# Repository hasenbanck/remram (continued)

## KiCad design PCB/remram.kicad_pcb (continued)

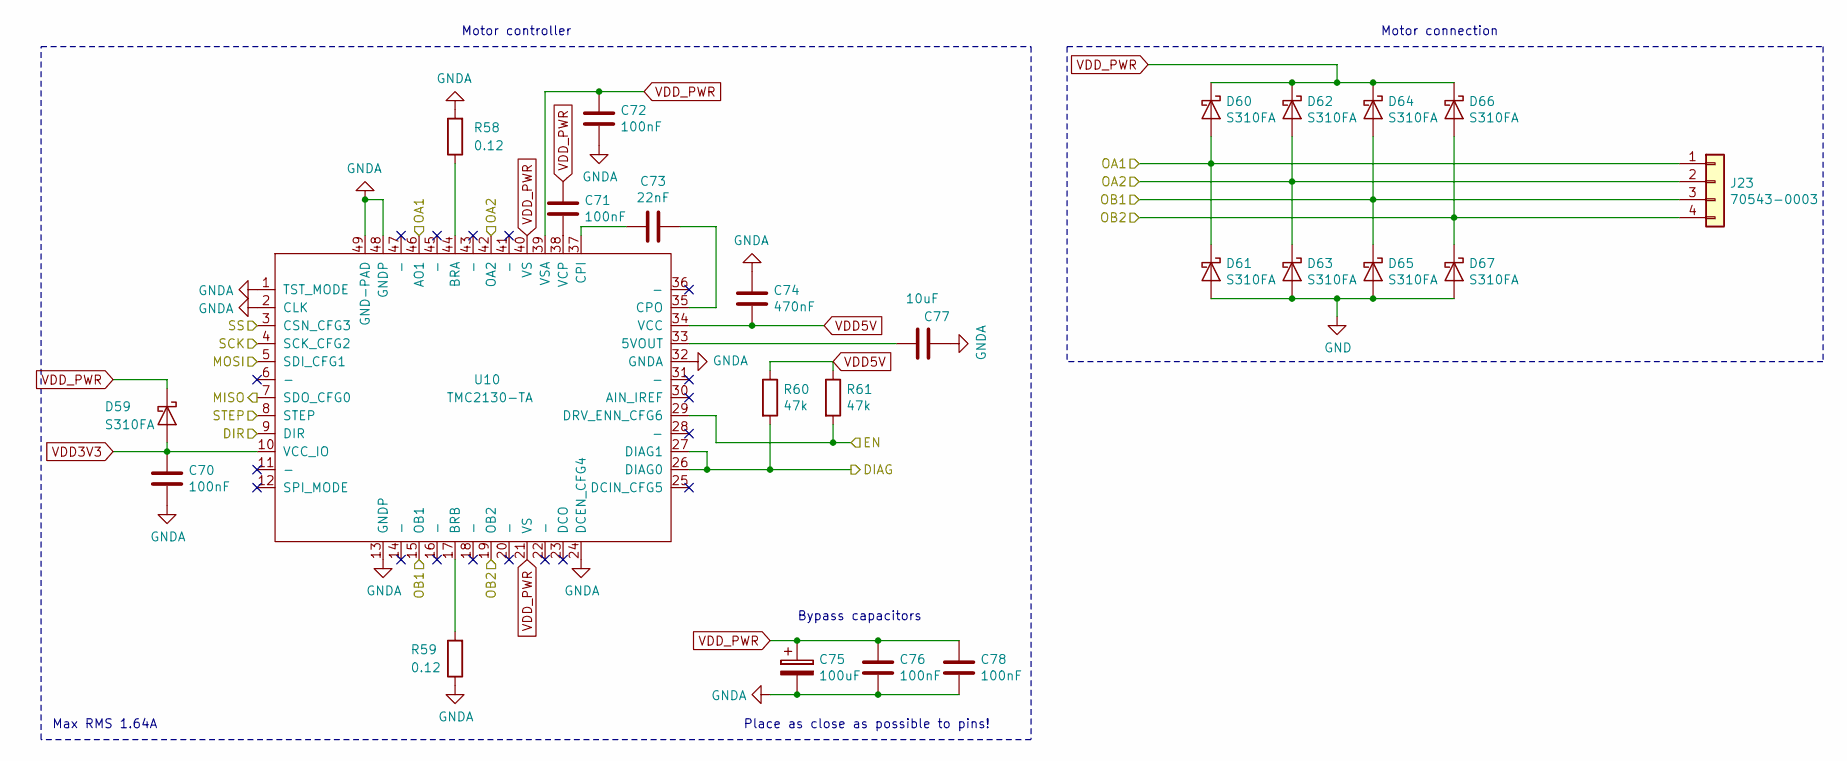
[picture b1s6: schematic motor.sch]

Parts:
C43, C44, C45, C49, C51: 100nF; C_0603_1608Metric
C46: 22nF; C_0603_1608Metric
C47: 470nF; C_0603_1608Metric
C48: 100uF; CP_Radial_D6.3mm_P2.50mm
C50: 10uF; C_0603_1608Metric
D32, D33, D34, D35, D36, D37, D38, D39, D40: S310FA; D_SOD-123
J20: 70543-0003
R46, R47: 0.12; R_1206_3216Metric
R48, R49: 47k; R_0603_1608Metric
U7: TMC2130-TA; TQFP-48-1EP_7x7mm_P0.5mm_EP4.8x4.8mm-Heatsink

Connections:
/MCU/MISO: U7.7 (SDO_CFG0); also elsewhere on the board
/MCU/MOSI: U7.5 (SDI_CFG1); also elsewhere on the board
/MCU/SCK: U7.4 (SCK_CFG2); also elsewhere on the board
/Motor X/DIAG: R48.2, U7.26 (DIAG0), U7.27 (DIAG1); also elsewhere on the board
/Motor X/DIR: U7.9 (DIR); also elsewhere on the board
/Motor X/EN: R49.2, U7.29 (DRV_ENN_CFG6); also elsewhere on the board
/Motor X/OA1: D33.2 (A), D34.1 (K), J20.1, U7.46 (AO1)
/Motor X/OA2: D35.2 (A), D36.1 (K), J20.2, U7.42 (OA2)
/Motor X/OB1: D37.2 (A), D38.1 (K), J20.3, U7.15 (OB1)
/Motor X/OB2: D39.2 (A), D40.1 (K), J20.4, U7.19 (OB2)
/Motor X/SS: U7.3 (CSN_CFG3); also elsewhere on the board
/Motor X/STEP: U7.8 (STEP); also elsewhere on the board
GND: C43.2, C45.2, C47.2, C48.2, C49.2, C50.2, C51.2, D34.2 (A), D36.2 (A), D38.2 (A), D40.2 (A), R46.2, R47.1, U7.1 (TST_MODE), U7.2 (CLK), U7.13 (GNDP), U7.24 (DCEN_CFG4), U7.32 (GNDA), U7.48 (GNDP), U7.49 (GND-PAD); also elsewhere on the board
unnamed: C44.2, U7.38 (VCP)
unnamed: C46.1, U7.35 (CPO)
unnamed: C46.2, U7.37 (CPI)
unnamed: C50.1, U7.33 (5VOUT)
unnamed: R46.1, U7.44 (BRA)
unnamed: R47.2, U7.17 (BRB)
VDD3V3: C43.1, D32.2 (A), U7.10 (VCC_IO); also elsewhere on the board
VDD5V: C47.1, R48.1, R49.1, U7.34 (VCC); also elsewhere on the board
VDD_PWR: C44.1, C45.1, C48.1, C49.1, C51.1, D32.1 (K), D33.1 (K), D35.1 (K), D37.1 (K), D39.1 (K), U7.21 (VS), U7.39 (VSA), U7.40 (VS); also elsewhere on the board

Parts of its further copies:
C52, C53, C54, C58, C60, C61, C62, C63, C67, C69, C70, C71, C72, C76, C78: 100nF; C_0603_1608Metric
C55, C64, C73: 22nF; C_0603_1608Metric
C56, C65, C74: 470nF; C_0603_1608Metric
C57, C66, C75: 100uF; CP_Radial_D6.3mm_P2.50mm
C59, C68, C77: 10uF; C_0603_1608Metric
D41, D42, D43, D44, D45, D46, D47, D48, D49, D50, D51, D52, D53, D54, D55, D56, D57, D58, D59, D60, D61, D62, D63, D64, D65, D66, D67: S310FA; D_SOD-123
J21, J22, J23: 70543-0003
R50, R51, R54, R55, R58, R59: 0.12; R_1206_3216Metric
R52, R53, R56, R57, R60, R61: 47k; R_0603_1608Metric
U8, U9, U10: TMC2130-TA; TQFP-48-1EP_7x7mm_P0.5mm_EP4.8x4.8mm-Heatsink

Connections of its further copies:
/MCU/E_STEP: U10.8 (STEP); also elsewhere on the board
/MCU/MISO: U8.7 (SDO_CFG0), U9.7 (SDO_CFG0), U10.7 (SDO_CFG0); also elsewhere on the board
/MCU/MOSI: U8.5 (SDI_CFG1), U9.5 (SDI_CFG1), U10.5 (SDI_CFG1); also elsewhere on the board
/MCU/SCK: U8.4 (SCK_CFG2), U9.4 (SCK_CFG2), U10.4 (SCK_CFG2); also elsewhere on the board
/Motor E/DIAG: R60.2, U10.26 (DIAG0), U10.27 (DIAG1); also elsewhere on the board
/Motor E/DIR: U10.9 (DIR); also elsewhere on the board
/Motor E/EN: R61.2, U10.29 (DRV_ENN_CFG6); also elsewhere on the board
/Motor E/OA1: D60.2 (A), D61.1 (K), J23.1, U10.46 (AO1)
/Motor E/OA2: D62.2 (A), D63.1 (K), J23.2, U10.42 (OA2)
/Motor E/OB1: D64.2 (A), D65.1 (K), J23.3, U10.15 (OB1)
/Motor E/OB2: D66.2 (A), D67.1 (K), J23.4, U10.19 (OB2)
/Motor E/SS: U10.3 (CSN_CFG3); also elsewhere on the board
/Motor Y/DIAG: R52.2, U8.26 (DIAG0), U8.27 (DIAG1); also elsewhere on the board
/Motor Y/DIR: U8.9 (DIR); also elsewhere on the board
/Motor Y/EN: R53.2, U8.29 (DRV_ENN_CFG6); also elsewhere on the board
/Motor Y/OA1: D42.2 (A), D43.1 (K), J21.1, U8.46 (AO1)
/Motor Y/OA2: D44.2 (A), D45.1 (K), J21.2, U8.42 (OA2)
/Motor Y/OB1: D46.2 (A), D47.1 (K), J21.3, U8.15 (OB1)
/Motor Y/OB2: D48.2 (A), D49.1 (K), J21.4, U8.19 (OB2)
/Motor Y/SS: U8.3 (CSN_CFG3); also elsewhere on the board
/Motor Y/STEP: U8.8 (STEP); also elsewhere on the board
/Motor Z/DIAG: R56.2, U9.26 (DIAG0), U9.27 (DIAG1); also elsewhere on the board
/Motor Z/DIR: U9.9 (DIR); also elsewhere on the board
/Motor Z/EN: R57.2, U9.29 (DRV_ENN_CFG6); also elsewhere on the board
/Motor Z/OA1: D51.2 (A), D52.1 (K), J22.1, U9.46 (AO1); also elsewhere on the board
/Motor Z/OA2: D53.2 (A), D54.1 (K), J22.2, U9.42 (OA2); also elsewhere on the board
/Motor Z/OB1: D55.2 (A), D56.1 (K), J22.3, U9.15 (OB1); also elsewhere on the board
/Motor Z/OB2: D57.2 (A), D58.1 (K), J22.4, U9.19 (OB2); also elsewhere on the board
/Motor Z/SS: U9.3 (CSN_CFG3); also elsewhere on the board
/Motor Z/STEP: U9.8 (STEP); also elsewhere on the board
GND: C52.2, C54.2, C56.2, C57.2, C58.2, C59.2, C60.2, C61.2, C63.2, C65.2, C66.2, C67.2, C68.2, C69.2, C70.2, C72.2, C74.2, C75.2, C76.2, C77.2, C78.2, D43.2 (A), D45.2 (A), D47.2 (A), D49.2 (A), D52.2 (A), D54.2 (A), D56.2 (A), D58.2 (A), D61.2 (A), D63.2 (A), D65.2 (A), D67.2 (A), R50.2, R51.1, R54.2, R55.1, R58.2, R59.1, U8.1 (TST_MODE), U8.2 (CLK), U8.13 (GNDP), U8.24 (DCEN_CFG4), U8.32 (GNDA), U8.48 (GNDP), U8.49 (GND-PAD), U9.1 (TST_MODE), U9.2 (CLK), U9.13 (GNDP), U9.24 (DCEN_CFG4), U9.32 (GNDA), U9.48 (GNDP), U9.49 (GND-PAD), U10.1 (TST_MODE), U10.2 (CLK), U10.13 (GNDP), U10.24 (DCEN_CFG4), U10.32 (GNDA), U10.48 (GNDP), U10.49 (GND-PAD); also elsewhere on the board
unnamed: C53.2, U8.38 (VCP)
unnamed: C55.1, U8.35 (CPO)
unnamed: C55.2, U8.37 (CPI)
unnamed: C59.1, U8.33 (5VOUT)
unnamed: C62.2, U9.38 (VCP)
unnamed: C64.1, U9.35 (CPO)
unnamed: C64.2, U9.37 (CPI)
unnamed: C68.1, U9.33 (5VOUT)
unnamed: C71.2, U10.38 (VCP)
unnamed: C73.1, U10.35 (CPO)
unnamed: C73.2, U10.37 (CPI)
unnamed: C77.1, U10.33 (5VOUT)
unnamed: R50.1, U8.44 (BRA)
unnamed: R51.2, U8.17 (BRB)
unnamed: R54.1, U9.44 (BRA)
unnamed: R55.2, U9.17 (BRB)
unnamed: R58.1, U10.44 (BRA)
unnamed: R59.2, U10.17 (BRB)
VDD3V3: C52.1, C61.1, C70.1, D41.2 (A), D50.2 (A), D59.2 (A), U8.10 (VCC_IO), U9.10 (VCC_IO), U10.10 (VCC_IO); also elsewhere on the board
VDD5V: C56.1, C65.1, C74.1, R52.1, R53.1, R56.1, R57.1, R60.1, R61.1, U8.34 (VCC), U9.34 (VCC), U10.34 (VCC); also elsewhere on the board
VDD_PWR: C53.1, C54.1, C57.1, C58.1, C60.1, C62.1, C63.1, C66.1, C67.1, C69.1, C71.1, C72.1, C75.1, C76.1, C78.1, D41.1 (K), D42.1 (K), D44.1 (K), D46.1 (K), D48.1 (K), D50.1 (K), D51.1 (K), D53.1 (K), D55.1 (K), D57.1 (K), D59.1 (K), D60.1 (K), D62.1 (K), D64.1 (K), D66.1 (K), U8.21 (VS), U8.39 (VSA), U8.40 (VS), U9.21 (VS), U9.39 (VSA), U9.40 (VS), U10.21 (VS), U10.39 (VSA), U10.40 (VS); also elsewhere on the board

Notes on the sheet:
Motor controller
Motor connection
Max RMS 1.64A
Place as close as possible to pins!
Bypass capacitors

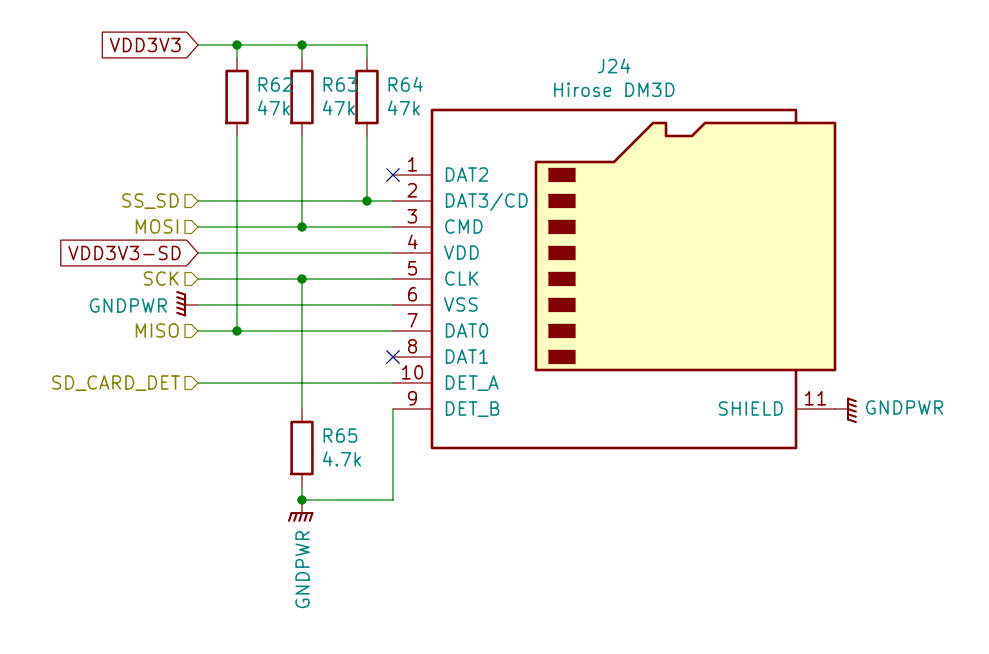
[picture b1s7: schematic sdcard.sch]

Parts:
J24: Hirose DM3D; microSD_HC_Hirose_DM3D-SF
R62, R63, R64: 47k; R_0603_1608Metric
R65: 4.7k; R_0603_1608Metric

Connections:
/MCU/MISO: J24.7 (DAT0), R62.2; also elsewhere on the board
/MCU/MOSI: J24.3 (CMD), R63.2; also elsewhere on the board
/MCU/SCK: J24.5 (CLK), R65.1; also elsewhere on the board
/MCU/SD_CARD_DET: J24.10 (DET_A); also elsewhere on the board
/MCU/SS_SD: J24.2 (DAT3/CD), R64.2; also elsewhere on the board
GND: J24.6 (VSS), J24.9 (DET_B), J24.11 (SHIELD), R65.2; also elsewhere on the board
VDD3V3: R62.1, R63.1, R64.1; also elsewhere on the board
VDD3V3-SD: J24.4 (VDD); also elsewhere on the board

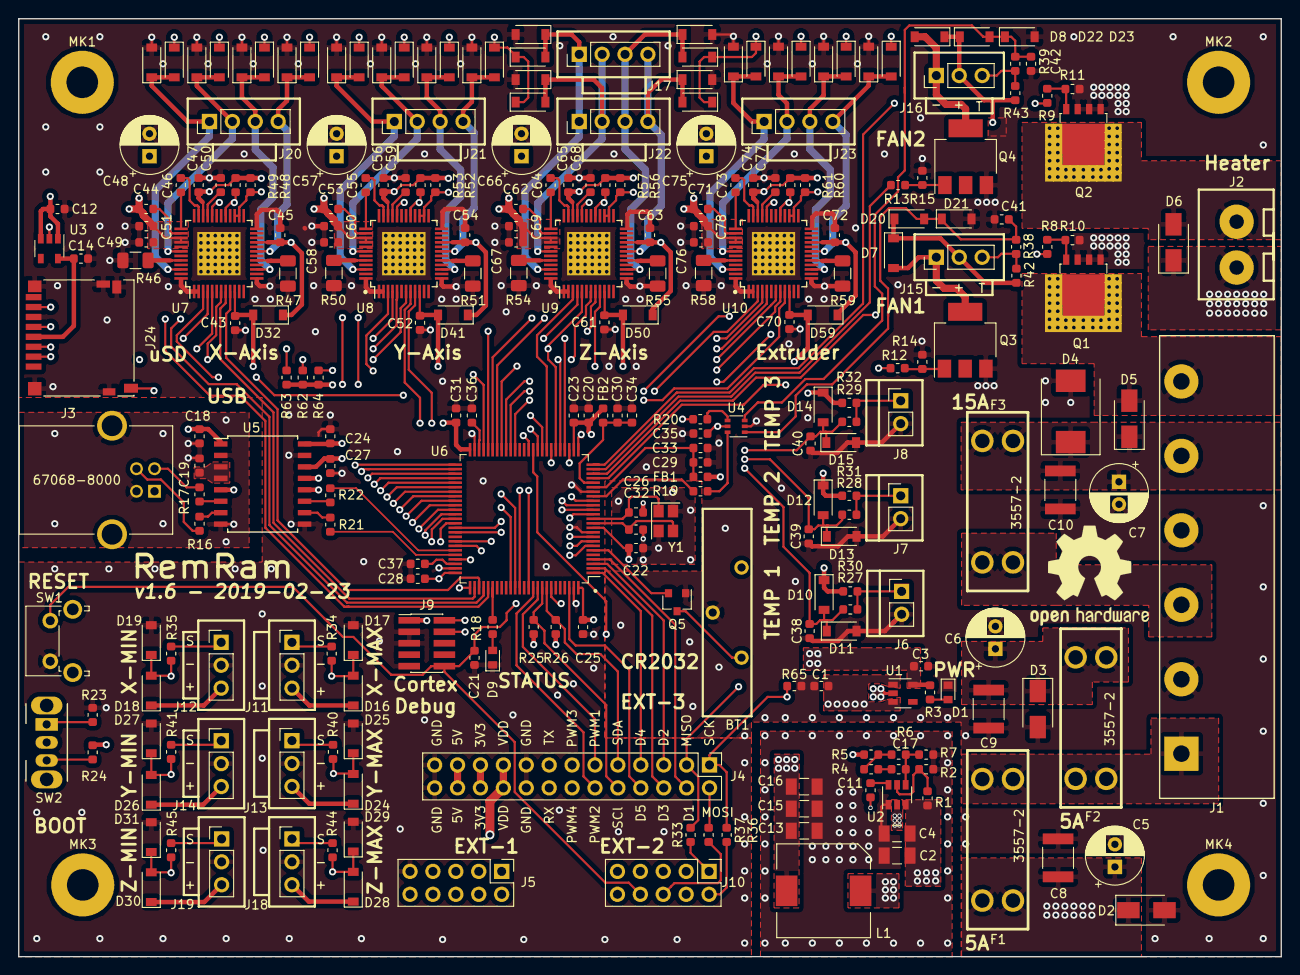
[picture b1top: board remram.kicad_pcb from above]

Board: 4 copper layers, 140.0 x 104.0 mm, 264 parts (0 on the bottom side), 173 nets.

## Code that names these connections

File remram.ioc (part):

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Mcu.Name=STM32F765V(G-I)Tx
Mcu.Package=LQFP100
Mcu.UserName=STM32F765VITx
PA0/WKUP.GPIOParameters=GPIO_Label
PA0/WKUP.GPIO_Label=PWM_FAN1
PA0/WKUP.Signal=S_TIM5_CH1
PA1.GPIOParameters=GPIO_Label
PA1.GPIO_Label=PWN_BED
PA1.Signal=S_TIM5_CH2
PA10.GPIOParameters=GPIO_Label
PA10.GPIO_Label=USART_RX
PA10.Mode=Asynchronous
PA10.Signal=USART1_RX
PA11.GPIOParameters=GPIO_Label
PA11.GPIO_Label=MCU_DD-
PA11.Mode=Device_Only
PA11.Signal=USB_OTG_FS_DM
PA12.GPIOParameters=GPIO_Label
PA12.GPIO_Label=MCU_DD+
PA12.Mode=Device_Only
PA12.Signal=USB_OTG_FS_DP
PA13.GPIOParameters=GPIO_Label
PA13.GPIO_Label=SWDIO
PA13.Mode=Serial_Wire
PA13.Signal=SYS_JTMS-SWDIO
PA14.GPIOParameters=GPIO_Label
PA14.GPIO_Label=SWCLK
PA14.Mode=Serial_Wire
PA14.Signal=SYS_JTCK-SWCLK
PA15.GPIOParameters=GPIO_Label
PA15.GPIO_Label=X_STEP
PA15.Signal=S_TIM2_CH1_ETR
PA2.GPIOParameters=GPIO_Label
PA2.GPIO_Label=PWM_FAN2
PA2.Signal=S_TIM5_CH3
PA3.GPIOParameters=GPIO_Label
PA3.GPIO_Label=PWM_HEAT
PA3.Signal=S_TIM5_CH4
PA4.GPIOParameters=GPIO_Label
PA4.GPIO_Label=FAN_SPEED1
PA4.Signal=ADCx_IN4
PA5.Mode=Full_Duplex_Master
PA5.Signal=SPI1_SCK
PA6.Mode=Full_Duplex_Master
PA6.Signal=SPI1_MISO
PA7.Mode=Full_Duplex_Master
PA7.Signal=SPI1_MOSI
PA9.GPIOParameters=GPIO_Label
PA9.GPIO_Label=USART_TX
PA9.Mode=Asynchronous
PA9.Signal=USART1_TX
PB0.GPIOParameters=GPIO_Label
PB0.GPIO_Label=SS_Y
PB0.Signal=GPIO_Output
PB1.GPIOParameters=GPIO_Label
PB1.GPIO_Label=SS_X
PB1.Signal=GPIO_Output
PB10.GPIOParameters=GPIO_Label
PB10.GPIO_Label=Z_STEP
PB10.Signal=S_TIM2_CH3
PB11.GPIOParameters=GPIO_Label
PB11.GPIO_Label=E_STEP
PB11.Signal=S_TIM2_CH4
PB12.GPIOParameters=GPIO_Label
PB12.GPIO_Label=X_MIN
PB12.Signal=GPIO_Input
PB13.GPIOParameters=GPIO_Label
PB13.GPIO_Label=X_MAX
PB13.Signal=GPIO_Input
PB14.GPIOParameters=GPIO_Label
PB14.GPIO_Label=Y_MIN
PB14.Signal=GPIO_Input
PB15.GPIOParameters=GPIO_Label
PB15.GPIO_Label=Y_MAX
PB15.Signal=GPIO_Input
PB2.GPIOParameters=GPIO_Label
PB2.GPIO_Label=SS_SDLCD
PB2.Signal=GPIO_Output
PB3.GPIOParameters=GPIO_Label
PB3.GPIO_Label=Y_STEP
PB3.Signal=S_TIM2_CH2
PB4.GPIOParameters=GPIO_Label
PB4.GPIO_Label=PWM_EXT1
PB4.Signal=S_TIM3_CH1
PB5.GPIOParameters=GPIO_Label
PB5.GPIO_Label=PWM_EXT2
PB5.Signal=S_TIM3_CH2
PB6.GPIOParameters=GPIO_Label
PB6.GPIO_Label=SCL
PB6.Mode=I2C
PB6.Signal=I2C1_SCL
PB7.GPIOParameters=GPIO_Label
PB7.GPIO_Label=SDA
PB7.Mode=I2C
PB7.Signal=I2C1_SDA
PC0.GPIOParameters=GPIO_Label
PC0.GPIO_Label=THERM_1
PC0.Signal=ADCx_IN10
PC1.GPIOParameters=GPIO_Label
PC1.GPIO_Label=THERM_2
PC1.Signal=ADCx_IN11
PC10.GPIOParameters=GPIO_Label
PC10.GPIO_Label=X_DIR
PC10.Signal=GPIO_Output
PC11.GPIOParameters=GPIO_Label
PC11.GPIO_Label=X_DIAG
PC11.Signal=GPIO_Input
PC12.GPIOParameters=GPIO_Label
PC12.GPIO_Label=X_EN
PC12.Signal=GPIO_Output
PC13.GPIOParameters=GPIO_Label
PC13.GPIO_Label=SD_CARD_DET
PC13.Signal=GPIO_Output
PC14/OSC32_IN.GPIOParameters=GPIO_Label
PC14/OSC32_IN.GPIO_Label=BTN_EN1
PC14/OSC32_IN.Signal=GPIO_Input
PC15/OSC32_OUT.GPIOParameters=GPIO_Label
PC15/OSC32_OUT.GPIO_Label=BTN_EN2
PC15/OSC32_OUT.Signal=GPIO_Input
PC2.GPIOParameters=GPIO_Label
PC2.GPIO_Label=THERM_3
PC2.Signal=ADCx_IN12
PC3.GPIOParameters=GPIO_Label
PC3.GPIO_Label=FAN_SPEED2
PC3.Signal=ADCx_IN13
PC4.GPIOParameters=GPIO_Label
PC4.GPIO_Label=SS_E
PC4.Signal=GPIO_Output
PC5.GPIOParameters=GPIO_Label
PC5.GPIO_Label=SS_Z
PC5.Signal=GPIO_Output
PC6.GPIOParameters=GPIO_Label
PC6.GPIO_Label=LCD_BEEPER
PC6.Signal=GPIO_Output
PC7.GPIOParameters=GPIO_Label
PC7.GPIO_Label=BTN_ENC
PC7.Signal=GPIO_Input
PC8.GPIOParameters=GPIO_Label
PC8.GPIO_Label=PWM_EXT3
PC8.Signal=S_TIM3_CH3
PC9.GPIOParameters=GPIO_Label
PC9.GPIO_Label=PWM_EXT4
PC9.Signal=S_TIM3_CH4
PD0.GPIOParameters=GPIO_Label
PD0.GPIO_Label=STATUS_LED
PD0.Signal=GPIO_Output
PD10.GPIOParameters=GPIO_Label
PD10.GPIO_Label=LCD_D7
PD10.Signal=GPIO_Output
PD11.GPIOParameters=GPIO_Label
PD11.GPIO_Label=LCD_D6
PD11.Signal=GPIO_Output
PD12.GPIOParameters=GPIO_Label
PD12.GPIO_Label=LCD_D5
PD12.Signal=GPIO_Output
PD13.GPIOParameters=GPIO_Label
PD13.GPIO_Label=LCD_D4
PD13.Signal=GPIO_Output
PD14.GPIOParameters=GPIO_Label
PD14.GPIO_Label=LCD_EN
PD14.Signal=GPIO_Output
PD15.GPIOParameters=GPIO_Label
PD15.GPIO_Label=LCD_RS
PD15.Signal=GPIO_Output
PD4.GPIOParameters=GPIO_Label
PD4.GPIO_Label=Y_EN
PD4.Signal=GPIO_Output
PD5.GPIOParameters=GPIO_Label
PD5.GPIO_Label=Y_DIAG
PD5.Signal=GPIO_Input
PD6.GPIOParameters=GPIO_Label
PD6.GPIO_Label=Y_DIR
PD6.Signal=GPIO_Output
PD8.GPIOParameters=GPIO_Label
PD8.GPIO_Label=Z_MIN
PD8.Signal=GPIO_Input
PD9.GPIOParameters=GPIO_Label
PD9.GPIO_Label=Z_MAX
PD9.Signal=GPIO_Input
PE1.GPIOParameters=GPIO_Label
PE1.GPIO_Label=EXT_D5
PE1.Signal=GPIO_Output
PE10.GPIOParameters=GPIO_Label
PE10.GPIO_Label=E_DIR
PE10.Signal=GPIO_Output
PE11.GPIOParameters=GPIO_Label
PE11.GPIO_Label=E_EN
PE11.Signal=GPIO_Output
PE12.GPIOParameters=GPIO_Label
PE12.GPIO_Label=E_DIAG
PE12.Signal=GPIO_Input
PE13.GPIOParameters=GPIO_Label
PE13.GPIO_Label=Z_DIR
PE13.Signal=GPIO_Output
PE14.GPIOParameters=GPIO_Label
PE14.GPIO_Label=Z_DIAG
PE14.Signal=GPIO_Output
PE15.GPIOParameters=GPIO_Label
PE15.GPIO_Label=Z_EN
PE15.Signal=GPIO_Output
PE2.GPIOParameters=GPIO_Label
PE2.GPIO_Label=EXT_D4
PE2.Signal=GPIO_Output
PE3.GPIOParameters=GPIO_Label
PE3.GPIO_Label=EXT_D3
PE3.Signal=GPIO_Output
PE4.GPIOParameters=GPIO_Label
PE4.GPIO_Label=EXT_D2
PE4.Signal=GPIO_Output
PE5.GPIOParameters=GPIO_Label
PE5.GPIO_Label=EXT_D1
PE5.Signal=GPIO_Output
PE7.GPIOParameters=GPIO_Label
PE7.GPIO_Label=SS_SD
PE7.Signal=GPIO_Output
PH0/OSC_IN.Mode=HSE-External-Oscillator
PH0/OSC_IN.Signal=RCC_OSC_IN
PH1/OSC_OUT.Mode=HSE-External-Oscillator
PH1/OSC_OUT.Signal=RCC_OSC_OUT
RCC.HSE_VALUE=24000000
RCC.SYSCLKFreq_VALUE=216000000
RCC.SYSCLKSource=RCC_SYSCLKSOURCE_PLLCLK
board=custom

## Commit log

2018-05-11 First commit of the new STM32 printer controller.
2018-05-12 Changed PCB.
    - Added MOSFET, connectors sheet
    - Changed MCU and power sheet
    - Reorganised sheets
2018-05-12 Removed some resistors for mosfets.
    I don't think they are needed.
    Also added some missing footprints.
2018-05-13 Added PD registors on MOSFET gates.
2018-05-13 Changed some sheets and added LICENCE.
2018-05-13 Finished first draft of the schematics.
2018-05-13 Fixed bugs found with ERC.
2018-05-13 Added missing foorprints.
2018-05-13 Fixed annotations and assignment errors.
2018-05-14 Saving work in progress.
    Every component now has a 3D mode.
2018-05-15 Removed logic level converter. Changed LDO.
2018-05-15 First try to layout a TMC driver.
2018-05-15 Layout for USB isolation.
2018-05-15 Finished TMC2130 placement.
    Motor sheets is now instanced. That way I simply could use
    a KiCad plugin to duplicate the layout in Pcbnew.
2018-05-16 Finished placement. Currently routing last paths.
2018-05-16 Added the secnd Z connection.
2018-05-16 First PCB version that is fully placed and routed.
2018-05-17 Moved some labels.
2018-05-17 Fixed some connections.
2018-05-17 Added a symbols text to silk screen.
2018-05-17 Reworked some traces for better layout.
    This will also come in handy, when we add more external
    connections (10 to 20pin external).
2018-05-17 Re-routed some traces.
    General cleanup.
2018-05-17 Reworked some traces and labels.
2018-05-17 Added missing labels.
2018-05-17 First draft of RemRam.
    I added a 20 pin expansion connector with the following pins:
    - SPI
    - I2C
    - USART
    - 4x PWM
    - 4x GPIO
2018-05-18 v0.2 of PCB.
    After some feedback, we changed following:
    - Switched FAN VDD from 24 to 5V.
    - FAN now have a ADC pin for speed sensing.
    - Expanded EXP-3 connector to 26 pin
    - Included 24V VDD.
    - Could be used to connect up to two
2018-05-18 Corrected MK3 hole and added some measurements.
2018-05-18 Version 0.3.
2018-05-18 Added a yellow status LED.
2018-05-18 Added missing change in MCU definition file.
2018-05-19 Changed the LED resistors to real values.
2018-05-19 Changed ordering of parts. Version 0.4.
2018-05-19 Moved some ADC lines for better noise isolation.
2018-05-19 Removed USART1 CK pin and added another digial pin.
    STM32duino doesn't seem to support USART. So I will only
    implement the UART pins.
2018-05-19 Reworked the ground plane for better ADC isolation.
2018-05-20 Changed LED to sane values. Updated diodes. v0.5.
2018-05-20 Added BOM for v0.5
2018-05-28 Added a battery for SRAM backup.
2018-05-30 Version 0.7
2018-05-30 Final version that goes to the lab.
2018-06-23 Change some traces and silkscreen text.
2018-06-23 Remove an old TODO
2018-06-23 Add a README.md
2018-06-24 Change DC-DC layout
    The ripple on the 5V and 3V3 rail was too high (360mV).
    In an attempt to reduce the RF and HF noise, I changed the layout
    to a more compact one. I also added a third 22uF output capacitor
    behind the inductor to lower ESR. I also added a 100nf input
    capacitor to combat HF noise, as recommended in the datasheet.
    The BOM needs to be updated in such a way, that we specificly
2018-06-24 Fix the SWD connector
    I screwed up and switched the SWDIO and SWCLK pins.
2018-06-24 Add information about debugging in README.md
    People might want to use the Cortex Debug Header to program and
    debug the STM32.
    I added information about the supported mode (only SWD) and missing
    SWO pin (So no SWO tracing / console output).
    We had to sacrifice thw SWO pin for a PWM output. This shouldn't
    matter much, since step-by-step debugging is working finde
2018-06-27 Add diodes and PU to endstops and fans (SCH only)
    For extra protection and PU, we added some diodes and a
    pull up resistor to the endstops and the fan tachometer.
2018-06-27 Change 1k resistors to 4.7k. Update Symbols
    Had to update the symbols to the right library again, since
    Kicad Nightly changed their library order.
    Also changed the 1k resistors to 4.7k to unify resistors and
    also upped the PU to a weaker value.
2018-06-27 Added protection diodes to TMC2130
    Diode on IO voltage protects chip to only accept command when
    motor voltage is present.
    Clamping diodes on motor outputs are for inductive loads.
2018-06-27 Add missing MOSFET footprint
2018-06-28 Switch GND and VDD_PWR on EXT-3
    Just to make updating over UART a little bit safer.
2018-06-30 Rework the PCB after feedback
    This design incooperated following changes:
    * Better power distribution
    * Diodes for driver, endstops and fan tachometer
    * Mounting holes not grounded and size 3.5mm
    * Better EXT3 header description
    * EXT1 and EXT2 footprint for normal 2.54 header
2018-06-30 Fix some traces
    Some on the 3V3 rail had some weird
    connection which I fixed.
2018-07-01 Fix PU on FAN RPM, Endstops and Grounding
    * Fixes too weak PU on RPM for fans
    * Simplified endstop setup
    * Grounding fixes:
    * GND below SPI bus
    * 3V3 LDO directly attached
    to main PWR source
2018-07-01 Add a P MOSFET to protect the TPS54308
    Since I fried two TPS54308 already, I think it would
    be best to implement a reverse voltage protection
    before the TPS that provides the 5V rail.
    To reuse parts, I also switches the battery protection
    P MOSFET to the same part.
2018-07-01 Chang battery holder
    This battery holder is more widely available.
2018-07-01 Update the ground fill
2018-07-02 Made small cosmetic changes
2018-07-03 Fix minor cosmetic issues
2018-07-04 Revert back to IRLML6401 for battery protection
    I reverted back to use the IRLML, since the gate-source threshhold
    coltage for the other P MOSFET was not low enough to always work
    inside the battery voltage.
2018-07-04 Updat the BOM for v1.0
    Updated BOM with mouser and digikey order numbers.
2018-07-05 Add compability for TPS54302
    Since the TPS54308 is often not available, we added the
    option to also use the TPS54038. This commit added a lot
    of components and changed the CSV.
2018-07-06 Optimize BOM for v1.0
    * Add alternative for heater / heatbed N-MOSFET
    * Changed 100k resistor for more cost effective variant
2018-07-26 Add Schmitt Trigger for fan tachometer
    The fan tachometer is too noise for the STM32F7 3.3V IO.
    We need to add a Schmitt Trigger to have a better noise handling
    and gain more low/high margin.
    Also some minor silkscreen adjustments. Backward compatible
    with v1.0.wq
2018-07-26 Change tachometer resistors to 4.7k and update BOM
    To better filter the tachometer signal, we had to increase the
    reistors of the tachometer RC filter and PU to 4.7k.
    This commit also updates the BOM for all changed since v1.0.wq
2018-07-27 Add an image to the README.md and discord link
2018-07-29 Switch BTN_ENC1 & BTN_ENC2
    Simple cosmetic change. The connector has them switched.
2018-08-25 Add series resistors to EXT-2 SPI lines
    To help with noisy ribbon cables and SD card communication we
    add three 100 ohm resistors in series for the SPI pins.
2018-10-03 Plain GND plane, new Debug Header, KILL PIN now RESET
2018-10-03 Place all components on top and better routing
2018-10-04 Add micro SD card reader and finished GND stitching
    Just to be safe, the SD card reader got it's own LDO.
2018-10-04 Changed PIN configuration
    Removed KILL_PIN and added / changed SS_SD and SS_SDLCD.
2018-10-04 Add BOM for v1.3
2018-10-04 New item designations and fixes some small manufacturing issues
2018-10-04 Some README fixes
2018-10-04 Small cosmetic changes
2018-10-07 Small cosmetic changes and fixed BOM.
2018-10-17 Update README.md with build instructions
2018-11-10 Fixes of v1.3 errors
    * Fixed missing GND connection for SD card detect
    * Optimized solder mask clearance from 0.2 to 0.05
    * Changed 3.3V LDO
2018-11-15 Added README.md instruction for configuring Marlin
2018-11-24 Finalised the silkscreen and fixed one copper pure
    Copper pure fixed:
    * VCC connection on USB isolation chip
    Silkscreen fix:
    * Orientation marker on connectors
2018-11-24 Changed PCB picture in README.md
2019-01-12 Fixed BOM and some footprint issues.
2019-01-12 Update README.md with newest information
2019-01-30 Add more information to the README.md
    * Using DFU files when flashing over DFU (USB)
    * Selecting "CDC Full Speed" in Arduino when using
    the CDC interface.
2019-02-23 Add PD for SPI SCK and some footprint fixes
    Footprint fixes are mainly orientation markings.
    PD needed for missbehaving Marlin firmware.
2020-04-30 Remove the discord link.
